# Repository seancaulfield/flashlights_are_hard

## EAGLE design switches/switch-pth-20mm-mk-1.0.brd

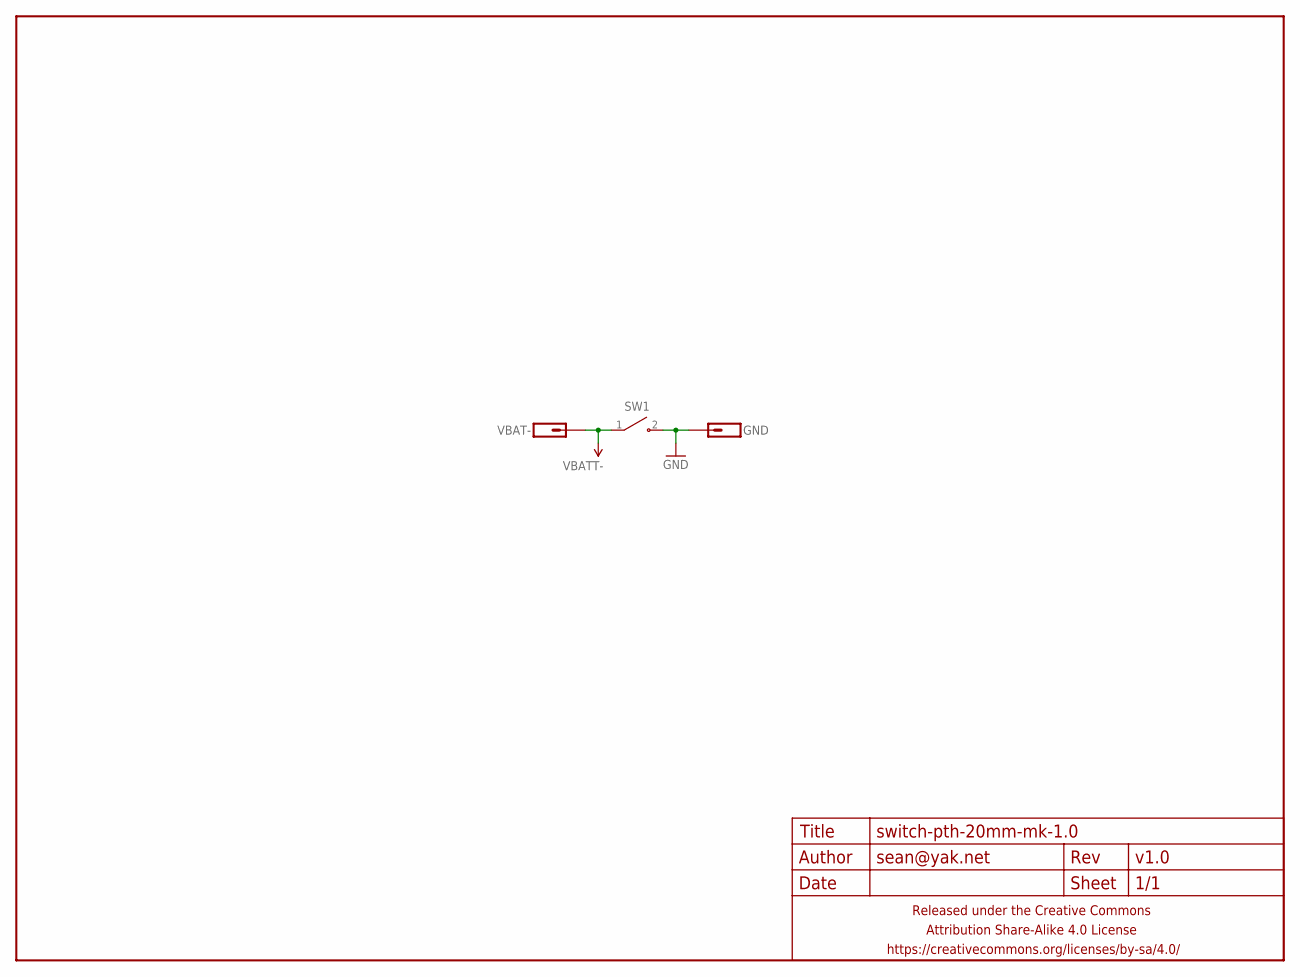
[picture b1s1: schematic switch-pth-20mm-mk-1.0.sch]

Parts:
FRAME1: FRAME-LETTERNO_PACKAGE; DUMMY
GND: M01NOT-A-VIA-NOPE; 1X01_NOSILK_NOSTOP
SW1: SWITCH-SPSTOMTEN-1288-PTH; OMTEN-1288-PTH
VBAT-: M01PTH-1MM-CIR-NS; 1X01-1MM-CIR-NS

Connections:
GND: GND.P$1, SW1.2 (NO)
VBAT: SW1.1 (COM), VBAT-.1

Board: 2 copper layers, 4 parts (2 on the bottom side), 2 nets, no tracks yet.

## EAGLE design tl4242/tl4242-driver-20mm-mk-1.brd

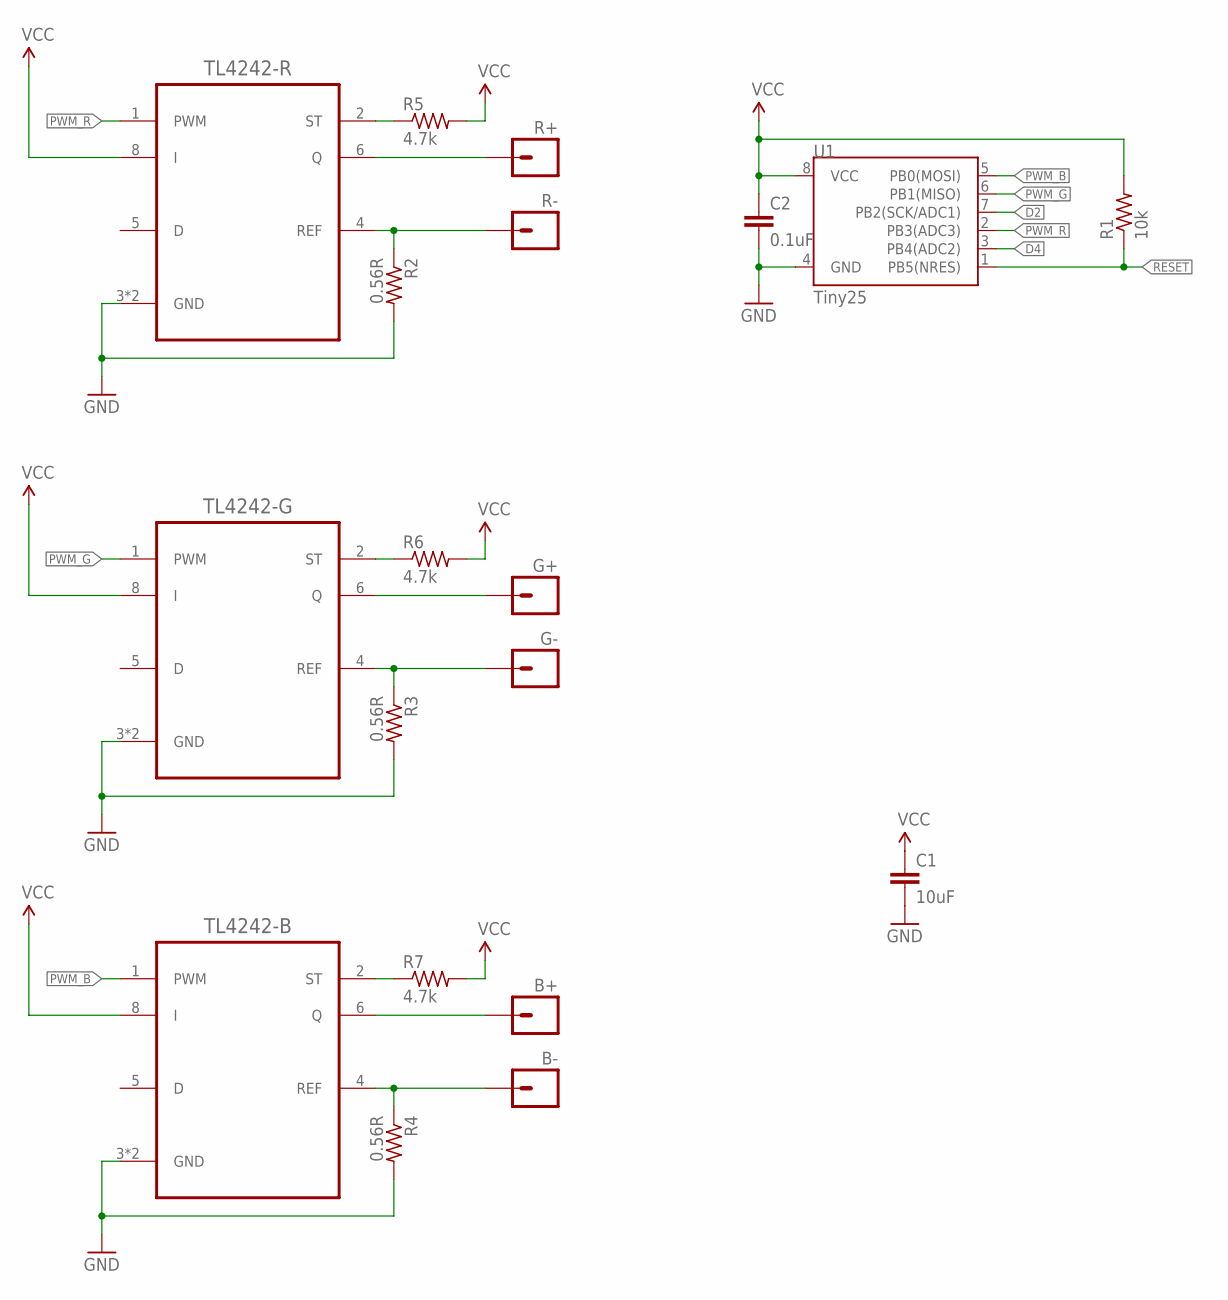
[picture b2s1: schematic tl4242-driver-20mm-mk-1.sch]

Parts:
B+: M01PTH-0.65MM-NS; 1X01_635UM
B-: M01PTH-0.65MM-NS; 1X01_635UM
C1: 10uF; C0805
C2: 0.1uF; C0603
G+: M01PTH-0.65MM-NS; 1X01_635UM
G-: M01PTH-0.65MM-NS; 1X01_635UM
R1: 10k; R0603
R2, R3, R4: 0.56R; R1206
R5, R6, R7: 4.7k; R0402
R+: M01PTH-0.65MM-NS; 1X01_635UM
R-: M01PTH-0.65MM-NS; 1X01_635UM
TL4242-B, TL4242-G, TL4242-R: TL4242DRJRSON8; SON80P410X410X80-9N
U1: Tiny25; SO08

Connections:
D2: U1.7 (PB2(SCK/ADC1))
D4: U1.3 (PB4(ADC2))
GND: C1.2, C2.2, R2.2, R3.2, R4.2, TL4242-B.3 (GND), TL4242-B.9 (GND), TL4242-G.3 (GND), TL4242-G.9 (GND), TL4242-R.3 (GND), TL4242-R.9 (GND), U1.4 (GND)
unnamed: G-.P$1, R3.1, TL4242-G.4 (REF)
unnamed: R2.1, R-.P$1, TL4242-R.4 (REF)
unnamed: R+.P$1, TL4242-R.6 (Q)
unnamed: G+.P$1, TL4242-G.6 (Q)
unnamed: B-.P$1, R4.1, TL4242-B.4 (REF)
unnamed: B+.P$1, TL4242-B.6 (Q)
unnamed: R7.1, TL4242-B.2 (ST)
unnamed: R6.1, TL4242-G.2 (ST)
unnamed: R5.1, TL4242-R.2 (ST)
PWM_B: TL4242-B.1 (PWM), U1.5 (PB0(MOSI))
PWM_G: TL4242-G.1 (PWM), U1.6 (PB1(MISO))
PWM_R: TL4242-R.1 (PWM), U1.2 (PB3(ADC3))
RESET: R1.1, U1.1 (PB5(NRES))
VCC: C1.1, C2.1, R1.2, R5.2, R6.2, R7.2, TL4242-B.8 (I), TL4242-G.8 (I), TL4242-R.8 (I), U1.8 (VCC)

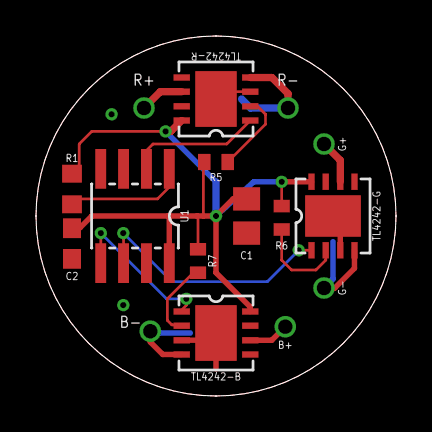
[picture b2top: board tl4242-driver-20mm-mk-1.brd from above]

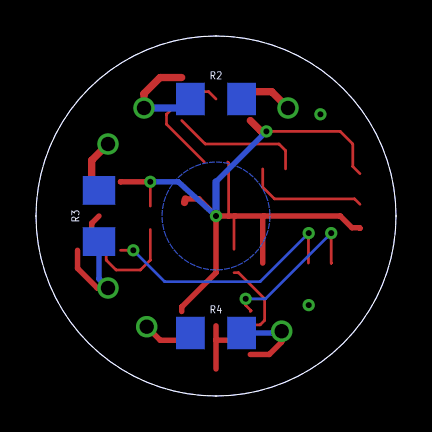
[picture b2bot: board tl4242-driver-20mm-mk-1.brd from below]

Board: 2 copper layers, 20.0 x 20.0 mm, 19 parts (3 on the bottom side), 15 nets.

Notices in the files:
parts and their libraries:
a_parts: Released under the Creative Commons Attribution Share-Alike 4.0 License
a_parts: https://creativecommons.org/licenses/by-sa/4.0
a_parts: Released under the Creative Commons
